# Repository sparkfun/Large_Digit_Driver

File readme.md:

SparkFun Large Digit Driver
============================

[*SparkFun Large Digit Driver (WIG-13279)*](https://www.sparkfun.com/products/13279)

The SparkFun Large Digit Driver is a chainable controller backpack that can be soldered directly to the back of our large 6.5" 7-segment displays.

Repository Contents
-------------------

* **/Firmware** - Example code 
* **/Hardware** - Eagle design files (.brd, .sch)
* **/Production** - Production panel files (.brd)

Documentation
--------------
* **[Hookup Guide](https://learn.sparkfun.com/tutorials/large-digit-driver-hookup-guide)** - Basic hookup guide for the Large Digit Driver.
* **[SparkFun Fritzing repo](https://github.com/sparkfun/Fritzing_Parts)** - Fritzing diagrams for SparkFun products.
* **[SparkFun 3D Model repo](https://github.com/sparkfun/3D_Models)** - 3D models of SparkFun products. 

License Information
-------------------

This product is _**open source**_! 

Please review the LICENSE.md file for license information. 

If you have any questions or concerns on licensing, please contact techsupport@sparkfun.com.

Distributed as-is; no warranty is given.

- Your friends at SparkFun.

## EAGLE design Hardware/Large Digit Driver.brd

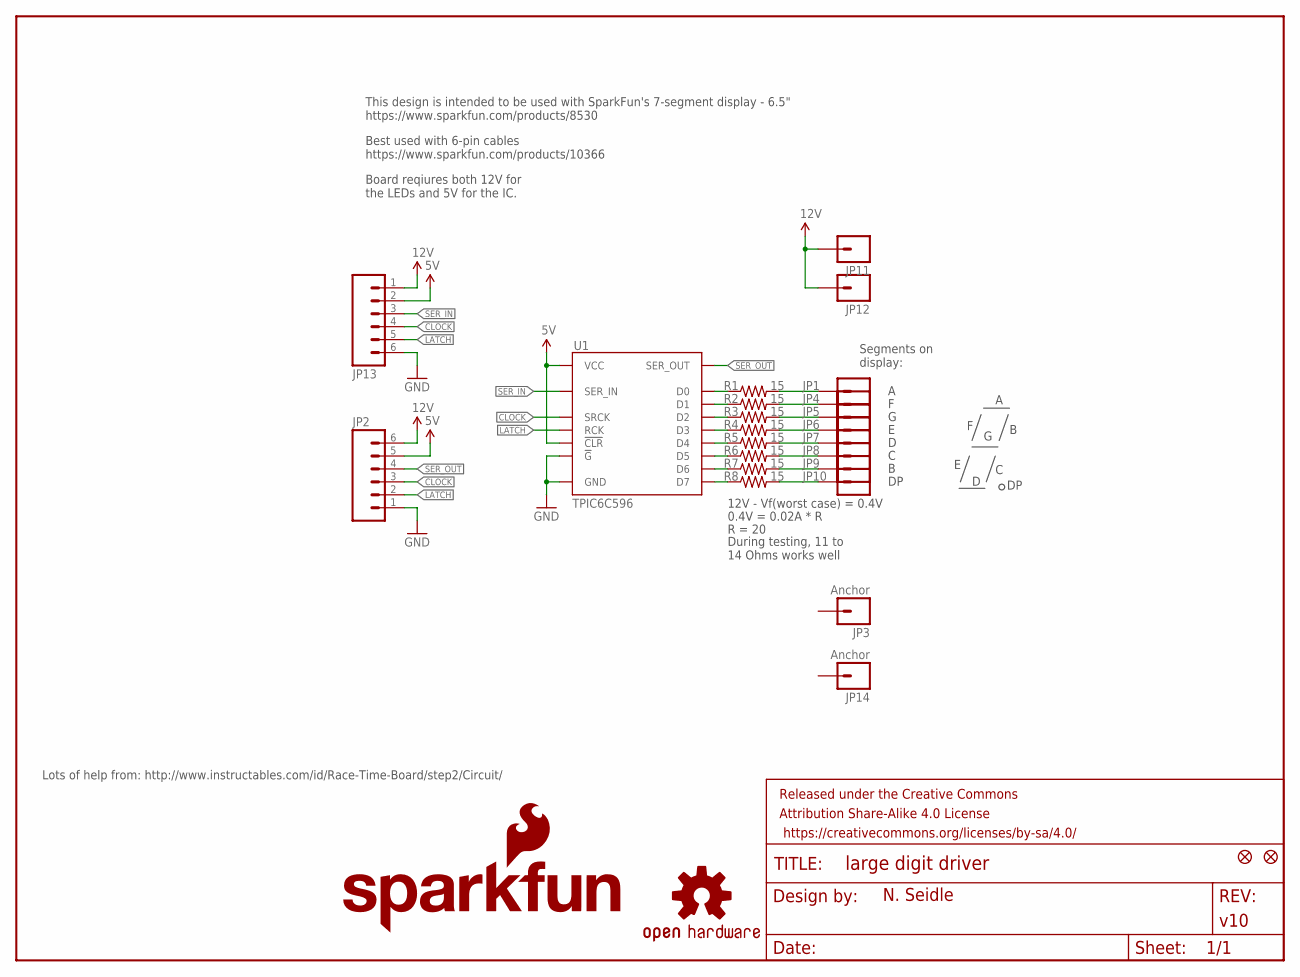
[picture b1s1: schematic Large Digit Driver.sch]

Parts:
FID1, FID2: FIDUCIAL1X2; FIDUCIAL-1X2
FRAME1: FRAME-LETTER; CREATIVE_COMMONS
JP1, JP4, JP5, JP6, JP7, JP8, JP9, JP10, JP11, JP12: M01PTH_LONGPAD; 1X01_LONGPAD
JP2, JP13: M06SMD; 1X06-SMD
JP3, JP14: Anchor; 1X01_LONGPAD
LOGO1: SFE_LOGO_NAME_FLAME.1_INCH; SFE_LOGO_NAME_FLAME_.1
LOGO2: OSHW-LOGOS; OSHW-LOGO-S
R1, R2, R3, R4, R5, R6, R7, R8: 15; 0603-RES
U1: TPIC6C596; SO016

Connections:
5V: JP2.5, JP13.2, U1.1 (VCC), U1.7 (!CLR)
12V: JP2.6, JP11.1, JP12.1, JP13.1
CLOCK: JP2.3, JP13.4, U1.15 (SRCK)
D0: R1.1, U1.3 (D0)
D1: R2.1, U1.4 (D1)
D2: R3.1, U1.5 (D2)
D3: R4.1, U1.6 (D3)
D4: R5.1, U1.11 (D4)
D5: R6.1, U1.12 (D5)
D6: R7.1, U1.13 (D6)
D7: R8.1, U1.14 (D7)
GND: JP2.1, JP13.6, U1.8 (!G), U1.16 (GND)
LATCH: JP2.2, JP13.5, U1.10 (RCK)
S0: JP1.1, R1.2
S1: JP4.1, R2.2
S2: JP5.1, R3.2
S3: JP6.1, R4.2
S4: JP7.1, R5.2
S5: JP8.1, R6.2
S6: JP9.1, R7.2
S7: JP10.1, R8.2
SER_IN: JP13.3, U1.2 (SER_IN)
SER_OUT: JP2.4, U1.9 (SER_OUT)

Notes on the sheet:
Lots of help from: http://www.instructables.com/id/Race-Time-Board/step2/Circuit/
Segments on display:
12V - Vf(worst case) = 0.4V
0.4V = 0.02A * R
R = 20
This design is intended to be used with SparkFun's 7-segment display - 6.5" https://www.sparkfun.com/products/8530
During testing, 11 to 14 Ohms works well
Best used with 6-pin cables https://www.sparkfun.com/products/10366
Board reqiures both 12V for the LEDs and 5V for the IC.

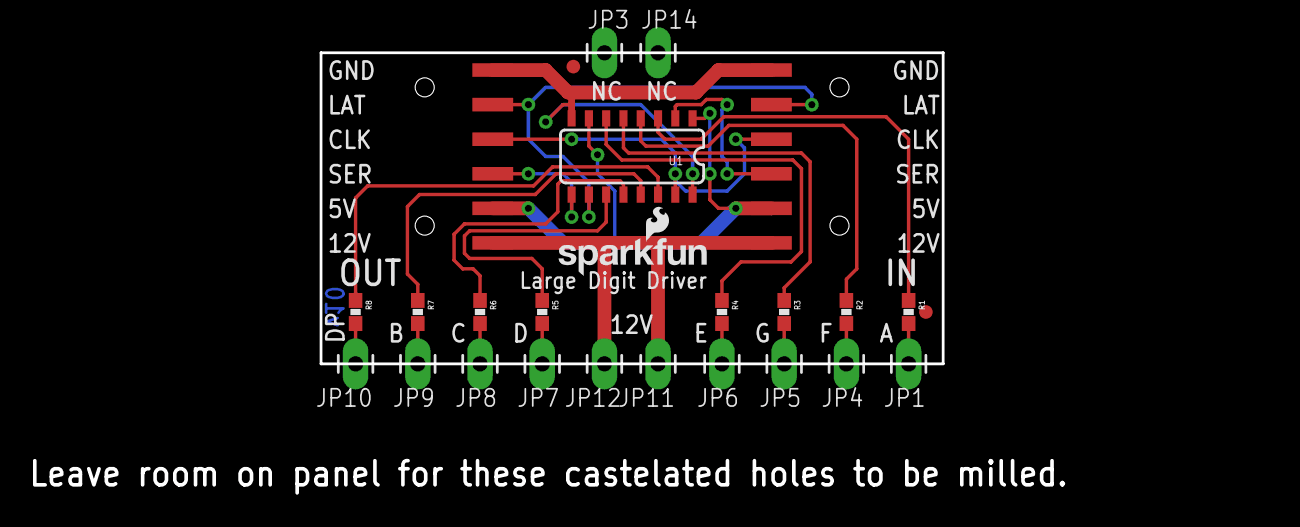
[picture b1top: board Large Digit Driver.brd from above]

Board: 2 copper layers, 91.3 x 32.7 mm, 28 parts (1 on the bottom side), 23 nets.

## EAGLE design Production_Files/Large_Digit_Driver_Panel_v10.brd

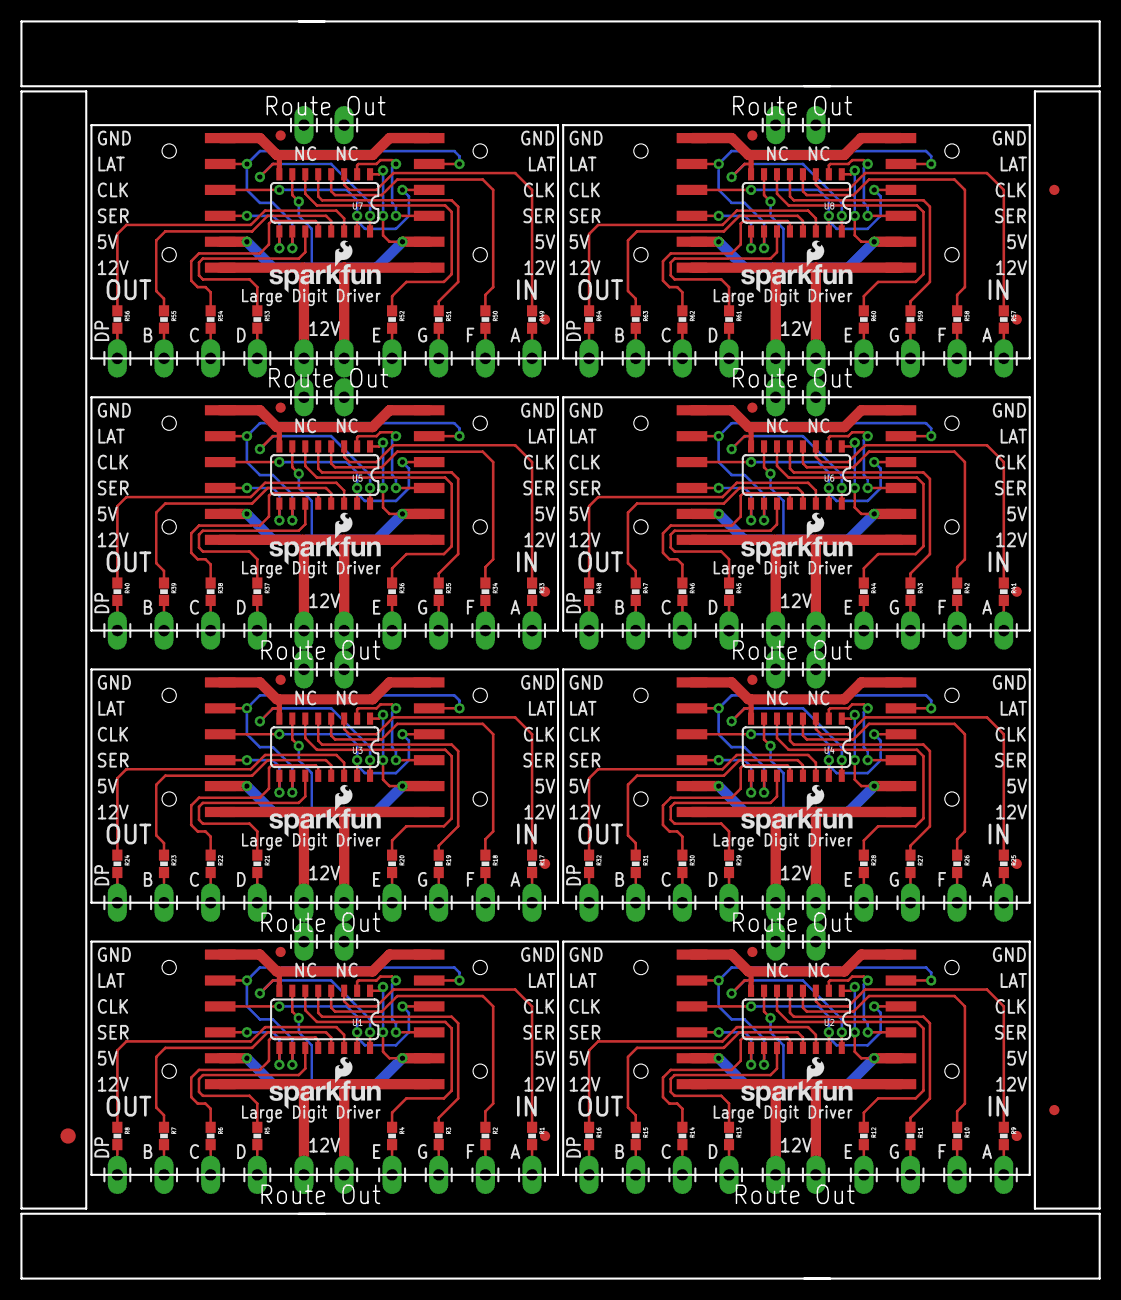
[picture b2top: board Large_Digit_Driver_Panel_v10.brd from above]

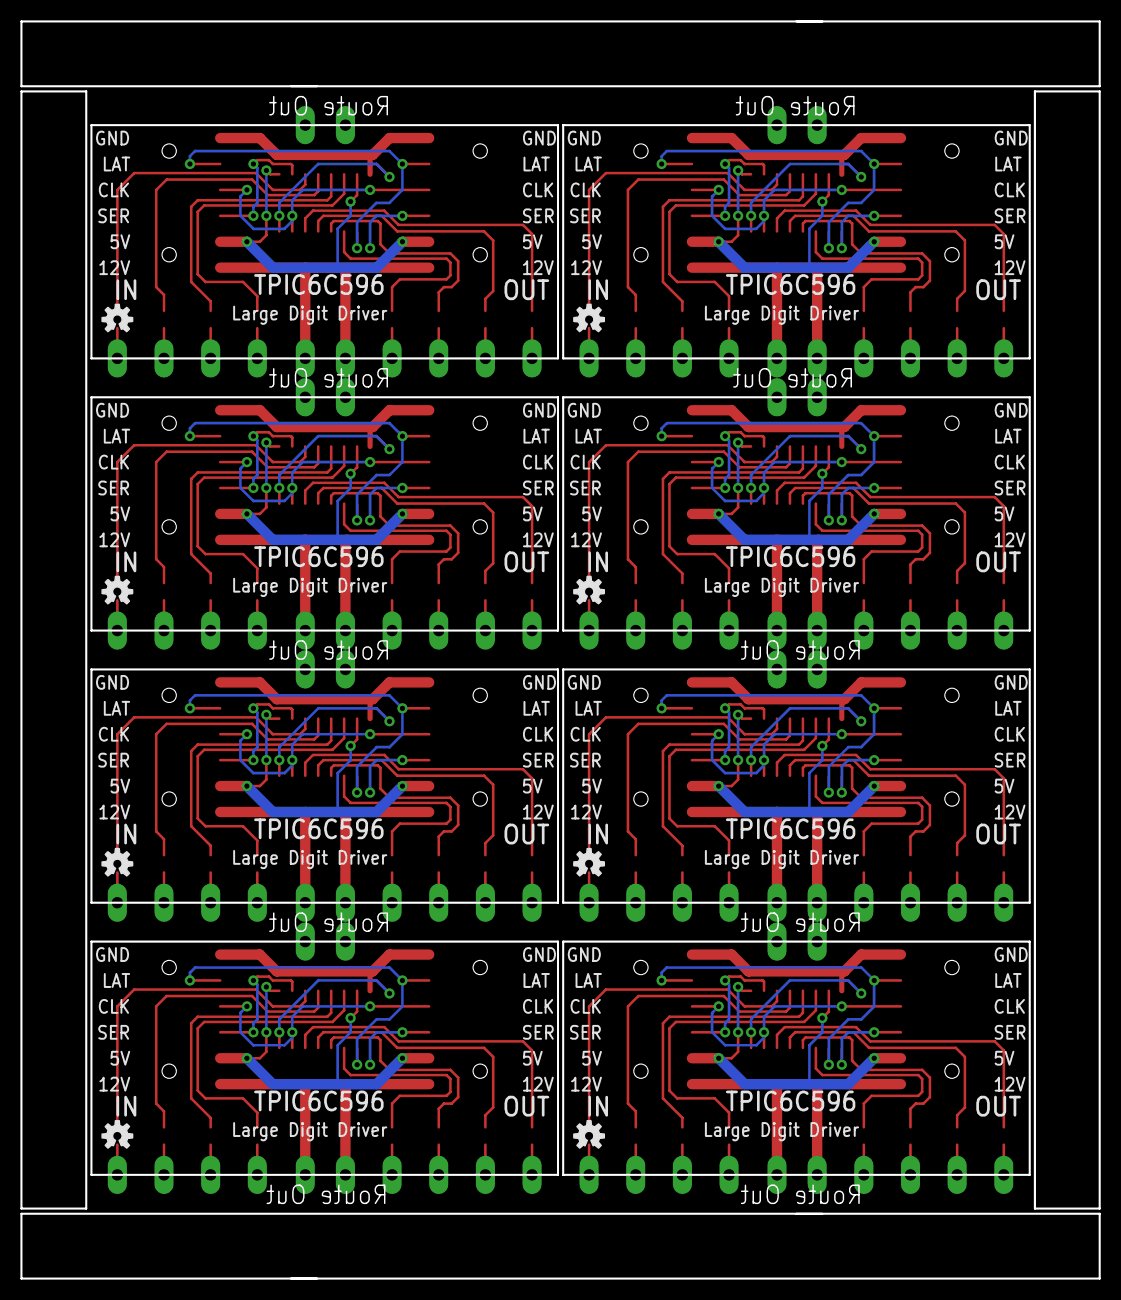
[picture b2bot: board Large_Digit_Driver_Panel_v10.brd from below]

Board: 2 copper layers, 105.7 x 123.2 mm, 219 parts (8 on the bottom side), 184 nets.

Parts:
E$1: FIDUCIAL-1.5X3
E$4, E$5: FIDUCIAL-1X2
FID1, FID2, FID3, FID4, FID5, FID6, FID7, FID8, FID9, FID10, FID11, FID12, FID13, FID14, FID15, FID16: FIDUCIAL1X2; FIDUCIAL-1X2
JP1, JP4, JP5, JP6, JP7, JP8, JP9, JP10, JP11, JP12, JP16, JP17, JP18, JP19, JP20, JP21, JP22, JP23, JP24, JP25, JP30, JP31, JP32, JP33, JP34, JP35, JP36, JP37, JP38, JP39, JP44, JP45, JP46, JP47, JP48, JP49, JP50, JP51, JP52, JP53, JP58, JP59, JP60, JP61, JP62, JP63, JP64, JP65, JP66, JP67, JP72, JP73, JP74, JP75, JP76, JP77, JP78, JP79, JP80, JP81, JP86, JP87, JP88, JP89, JP90, JP91, JP92, JP93, JP94, JP95, JP100, JP101, JP102, JP103, JP104, JP105, JP106, JP107, JP108, JP109: 1X01_LONGPAD
JP2, JP13, JP15, JP26, JP29, JP40, JP43, JP54, JP57, JP68, JP71, JP82, JP85, JP96, JP99, JP110: 1X06-SMD
JP3, JP14, JP27, JP28, JP41, JP42, JP55, JP56, JP69, JP70, JP83, JP84, JP97, JP98, JP111, JP112: Anchor; 1X01_LONGPAD
LOGO1, LOGO4, LOGO6, LOGO8, LOGO10, LOGO12, LOGO14, LOGO16: SFE_LOGO_NAME_FLAME.1_INCH; SFE_LOGO_NAME_FLAME_.1
LOGO2, LOGO3, LOGO5, LOGO7, LOGO9, LOGO11, LOGO13, LOGO15: OSHW-LOGOS; OSHW-LOGO-S
R1, R2, R3, R4, R5, R6, R7, R8, R9, R10, R11, R12, R13, R14, R15, R16, R17, R18, R19, R20, R21, R22, R23, R24, R25, R26, R27, R28, R29, R30, R31, R32, R33, R34, R35, R36, R37, R38, R39, R40, R41, R42, R43, R44, R45, R46, R47, R48, R49, R50, R51, R52, R53, R54, R55, R56, R57, R58, R59, R60, R61, R62, R63, R64: 15; 0603-RES
U1, U2, U3, U4, U5, U6, U7, U8: TPIC6C596; SO016

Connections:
5V: JP2.5, JP13.2, U1.1, U1.7
5V1: JP15.5, JP26.2, U2.1, U2.7
5V2: JP29.5, JP40.2, U3.1, U3.7
5V3: JP43.5, JP54.2, U4.1, U4.7
5V4: JP57.5, JP68.2, U5.1, U5.7
5V5: JP71.5, JP82.2, U6.1, U6.7
5V6: JP85.5, JP96.2, U7.1, U7.7
5V7: JP99.5, JP110.2, U8.1, U8.7
12V: JP2.6, JP11.1, JP12.1, JP13.1
12V1: JP15.6, JP24.1, JP25.1, JP26.1
12V2: JP29.6, JP38.1, JP39.1, JP40.1
12V3: JP43.6, JP52.1, JP53.1, JP54.1
12V4: JP57.6, JP66.1, JP67.1, JP68.1
12V5: JP71.6, JP80.1, JP81.1, JP82.1
12V6: JP85.6, JP94.1, JP95.1, JP96.1
12V7: JP99.6, JP108.1, JP109.1, JP110.1
CLOCK: JP2.3, JP13.4, U1.15
CLOCK1: JP15.3, JP26.4, U2.15
CLOCK2: JP29.3, JP40.4, U3.15
CLOCK3: JP43.3, JP54.4, U4.15
CLOCK4: JP57.3, JP68.4, U5.15
CLOCK5: JP71.3, JP82.4, U6.15
CLOCK6: JP85.3, JP96.4, U7.15
CLOCK7: JP99.3, JP110.4, U8.15
D0: R1.1, U1.3
D1: R2.1, U1.4
D2: R3.1, U1.5
D3: R4.1, U1.6
D4: R5.1, U1.11
D5: R6.1, U1.12
D6: R7.1, U1.13
D7: R8.1, U1.14
D8: R9.1, U2.3
D9: R10.1, U2.4
D10: R11.1, U2.5
D11: R12.1, U2.6
D12: R13.1, U2.11
D13: R14.1, U2.12
D14: R15.1, U2.13
D15: R16.1, U2.14
D16: R17.1, U3.3
D17: R18.1, U3.4
D18: R19.1, U3.5
D19: R20.1, U3.6
D20: R21.1, U3.11
D21: R22.1, U3.12
D22: R23.1, U3.13
D23: R24.1, U3.14
D24: R25.1, U4.3
D25: R26.1, U4.4
D26: R27.1, U4.5
D27: R28.1, U4.6
D28: R29.1, U4.11
D29: R30.1, U4.12
D30: R31.1, U4.13
D31: R32.1, U4.14
D32: R33.1, U5.3
D33: R34.1, U5.4
D34: R35.1, U5.5
D35: R36.1, U5.6
D36: R37.1, U5.11
D37: R38.1, U5.12
D38: R39.1, U5.13
D39: R40.1, U5.14
D40: R41.1, U6.3
D41: R42.1, U6.4
D42: R43.1, U6.5
D43: R44.1, U6.6
D44: R45.1, U6.11
D45: R46.1, U6.12
D46: R47.1, U6.13
D47: R48.1, U6.14
D48: R49.1, U7.3
D49: R50.1, U7.4
D50: R51.1, U7.5
D51: R52.1, U7.6
D52: R53.1, U7.11
D53: R54.1, U7.12
D54: R55.1, U7.13
D55: R56.1, U7.14
D56: R57.1, U8.3
D57: R58.1, U8.4
D58: R59.1, U8.5
D59: R60.1, U8.6
D60: R61.1, U8.11
D61: R62.1, U8.12
D62: R63.1, U8.13
D63: R64.1, U8.14
GND: JP2.1, JP13.6, U1.8, U1.16
GND1: JP15.1, JP26.6, U2.8, U2.16
GND2: JP29.1, JP40.6, U3.8, U3.16
GND3: JP43.1, JP54.6, U4.8, U4.16
GND4: JP57.1, JP68.6, U5.8, U5.16
GND5: JP71.1, JP82.6, U6.8, U6.16
GND6: JP85.1, JP96.6, U7.8, U7.16
GND7: JP99.1, JP110.6, U8.8, U8.16
LATCH: JP2.2, JP13.5, U1.10
LATCH1: JP15.2, JP26.5, U2.10
LATCH2: JP29.2, JP40.5, U3.10
LATCH3: JP43.2, JP54.5, U4.10
LATCH4: JP57.2, JP68.5, U5.10
LATCH5: JP71.2, JP82.5, U6.10
LATCH6: JP85.2, JP96.5, U7.10
LATCH7: JP99.2, JP110.5, U8.10
S0: JP1.1, R1.2
S1: JP4.1, R2.2
S2: JP5.1, R3.2
S3: JP6.1, R4.2
S4: JP7.1, R5.2
S5: JP8.1, R6.2
S6: JP9.1, R7.2
S7: JP10.1, R8.2
S8: JP16.1, R9.2
S9: JP17.1, R10.2
S10: JP18.1, R11.2
S11: JP19.1, R12.2
S12: JP20.1, R13.2
S13: JP21.1, R14.2
S14: JP22.1, R15.2
S15: JP23.1, R16.2
S16: JP30.1, R17.2
S17: JP31.1, R18.2
S18: JP32.1, R19.2
S19: JP33.1, R20.2
S20: JP34.1, R21.2
S21: JP35.1, R22.2
S22: JP36.1, R23.2
S23: JP37.1, R24.2
S24: JP44.1, R25.2
S25: JP45.1, R26.2
S26: JP46.1, R27.2
S27: JP47.1, R28.2
S28: JP48.1, R29.2
S29: JP49.1, R30.2
S30: JP50.1, R31.2
S31: JP51.1, R32.2
S32: JP58.1, R33.2
S33: JP59.1, R34.2
S34: JP60.1, R35.2
S35: JP61.1, R36.2
S36: JP62.1, R37.2
S37: JP63.1, R38.2
S38: JP64.1, R39.2
S39: JP65.1, R40.2
S40: JP72.1, R41.2
S41: JP73.1, R42.2
S42: JP74.1, R43.2
S43: JP75.1, R44.2
S44: JP76.1, R45.2
S45: JP77.1, R46.2
S46: JP78.1, R47.2
S47: JP79.1, R48.2
S48: JP86.1, R49.2
S49: JP87.1, R50.2
S50: JP88.1, R51.2
S51: JP89.1, R52.2
S52: JP90.1, R53.2
S53: JP91.1, R54.2
S54: JP92.1, R55.2
S55: JP93.1, R56.2
S56: JP100.1, R57.2
S57: JP101.1, R58.2
S58: JP102.1, R59.2
S59: JP103.1, R60.2
S60: JP104.1, R61.2
S61: JP105.1, R62.2
S62: JP106.1, R63.2
S63: JP107.1, R64.2
SER_IN: JP13.3, U1.2
SER_IN1: JP26.3, U2.2
SER_IN2: JP40.3, U3.2
SER_IN3: JP54.3, U4.2
SER_IN4: JP68.3, U5.2
SER_IN5: JP82.3, U6.2
SER_IN6: JP96.3, U7.2
SER_IN7: JP110.3, U8.2
SER_OUT: JP2.4, U1.9
SER_OUT1: JP15.4, U2.9
SER_OUT2: JP29.4, U3.9
SER_OUT3: JP43.4, U4.9
SER_OUT4: JP57.4, U5.9
SER_OUT5: JP71.4, U6.9
SER_OUT6: JP85.4, U7.9
SER_OUT7: JP99.4, U8.9

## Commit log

2015-01-26 :confetti_ball: Added .gitattributes & .gitignore files
2015-01-26 Initial Commit.
2015-01-28 Conversion to SMD parts.
    Board is much smaller. Uses TPIC6C596.
2015-01-28 Removed extraneous layers.
2015-01-30 Adding anchor pins for SMD mounting.
2015-02-04 Added fiducials for issue #1.
2015-02-05 moved fiducial from under header
2015-02-05 moved it again, better this time
2015-02-06 Note added to schematic: issue #2
2015-03-09 Changing to 15 Ohm limiting resistors. Adding example code.
    20 Ohm resistors brought current down to 11mA in testing. Decreasing
    resistor size to get higher current per segment.
2015-03-12 Fiducial bump. Adding silk on bottom.
    Fixes issue #3.
2015-03-18 Added silk to anchors. Added power notes to schematic.
2015-03-23 created panel v10
2015-04-01 Fixing logos for easier CAM
2015-04-02 fixed logos on panel for better cam
2015-06-26 Adding license file, updating README, fixing directory name, fixing file names

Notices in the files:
parts and their libraries:
SparkFun-Aesthetics: Licensing: CC v3.0 Share-Alike You are welcome to use this library for commercial purposes.
SparkFun-Aesthetics: Released under the Creative Commons Attribution Share-Alike 4.0 License
SparkFun-Aesthetics: https://creativecommons.org/licenses/by-sa/4.0
